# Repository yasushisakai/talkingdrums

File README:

sending and receiving protocol

[command, value, B00001010]

command
0: 'ready': first module to sender to say module is ready for getting byte
1: 'send' : message sent from sender to first module
2: 'receive' : message sent from the last module to the receiver

example:

[B00000000, B00000000, B00001010]
then
[B00000001, B10101010, B00001010]
.
.
.
[B00000010, B10101010, B00001010]

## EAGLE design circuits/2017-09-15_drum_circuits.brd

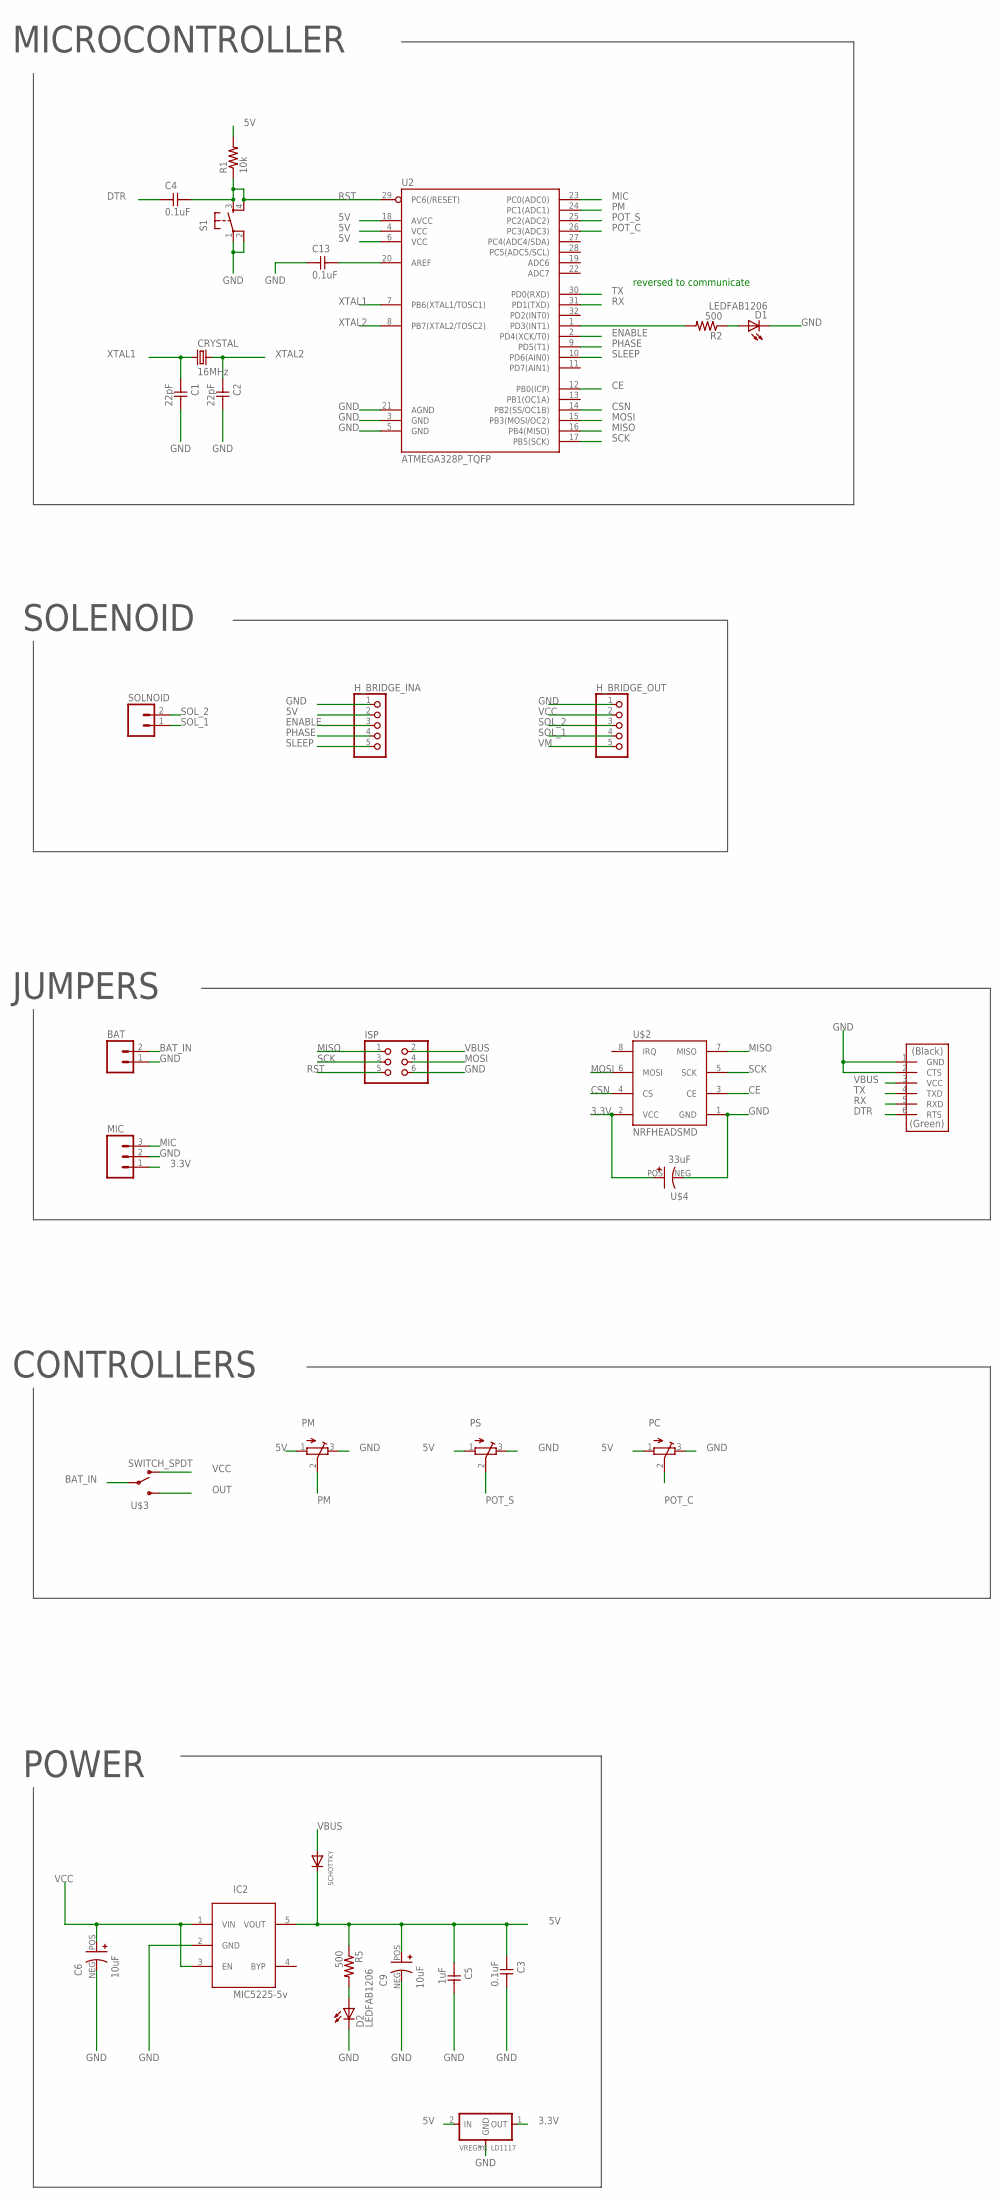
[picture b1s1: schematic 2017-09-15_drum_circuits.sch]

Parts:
BAT: M02PTH; 1X02
C1, C2: 22pF; C1206FAB
C3, C4, C13: 0.1uF; C1206FAB
C5: 1uF; C1206FAB
C6, C9: 10uF; PANASONIC-CAP-SMD-B
CRYSTAL: 16MHz; 2-SMD-5X3MM
D1, D2: LEDFAB1206; LED1206FAB
H_BRIDGE_INA: PINHD-1X05_2.54-SMD; 1X05SMD
H_BRIDGE_OUT: PINHD-1X05_2.54-SMD; 1X05SMD
IC2: MIC5225-5v; SOT23-5L
ISP: PINHD-2X3-SMD; 2X03SMD
MIC: M03PTH; 1X03
PC: TRIMPOTTC33X; TC33X
PM: TRIMPOTTC33X; TC33X
PS: TRIMPOTTC33X; TC33X
R1: 10k; R1206FAB
R2, R5: 500; R1206FAB
S1: 6MM_SWITCH6MM_SWITCH; 6MM_SWITCH
SCHOTTKY: DIODE_SOD-123FL; SOD-123FL
SOLNOID: M02PTH; 1X02
U2: ATMEGA328P_TQFP; TQFP32-08
U$1: FTDI-SMD-HEADER; 1X06SMD
U$2: NRFHEADSMD; 2.54MM
U$3: SWITCH_SPDT; KPS-1290
U$4: 33uF; PANASONIC-CAP-SMD-C
VREG3.3: LD1117; SOT23

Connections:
3.3V: MIC.1, U$2.2 (VCC), U$4.POS (+), VREG3.3.1 (OUT)
5V: C3.1, C5.1, C9.POS (+), H_BRIDGE_INA.2, IC2.5 (VOUT), PC.1 (A), PM.1 (A), PS.1 (A), R1.2, R5.1, SCHOTTKY.C, U2.4 (VCC), U2.6 (VCC), U2.18 (AVCC), VREG3.3.2 (IN)
BAT_IN: BAT.2, U$3.P
CE: U2.12 (PB0(ICP)), U$2.3 (CE)
CSN: U2.14 (PB2(SS/OC1B)), U$2.4 (CS)
DTR: C4.1, U$1.6 (RTS)
ENABLE: H_BRIDGE_INA.3, U2.2 (PD4(XCK/T0))
GND: BAT.1, C1.2, C2.2, C3.2, C5.2, C6.NEG (-), C9.NEG (-), C13.1, D1.2 (C), D2.2 (C), H_BRIDGE_INA.1, H_BRIDGE_OUT.1, IC2.2 (GND), ISP.6, MIC.2, PC.3 (E), PM.3 (E), PS.3 (E), S1.1, S1.2 (P1), U2.3 (GND), U2.5 (GND), U2.21 (AGND), U$1.1 (GND), U$1.2 (CTS), U$2.1 (GND), U$4.NEG (-), VREG3.3.3 (GND)
MIC: MIC.3, U2.23 (PC0(ADC0))
MISO: ISP.1, U2.16 (PB4(MISO)), U$2.7 (MISO)
MOSI: ISP.4, U2.15 (PB3(MOSI/OC2)), U$2.6 (MOSI)
unnamed: D1.1 (A), R2.1
unnamed: D2.1 (A), R5.2
unnamed: C13.2, U2.20 (AREF)
unnamed: R2.2, U2.1 (PD3(INT1))
OUT: U$3.S
PHASE: H_BRIDGE_INA.4, U2.9 (PD5(T1))
PM: PM.2 (S), U2.24 (PC1(ADC1))
POT_C: PC.2 (S), U2.26 (PC3(ADC3))
POT_S: PS.2 (S), U2.25 (PC2(ADC2))
RST: C4.2, ISP.5, R1.1, S1.3 (S), S1.4 (S1), U2.29 (PC6(/RESET))
RX: U2.31 (PD1(TXD)), U$1.5 (RXD)
SCK: ISP.3, U2.17 (PB5(SCK)), U$2.5 (SCK)
SLEEP: H_BRIDGE_INA.5, U2.10 (PD6(AIN0))
SOL_1: H_BRIDGE_OUT.4, SOLNOID.1
SOL_2: H_BRIDGE_OUT.3, SOLNOID.2
TX: U2.30 (PD0(RXD)), U$1.4 (TXD)
VBUS: ISP.2, SCHOTTKY.A, U$1.3 (VCC)
VCC: C6.POS (+), H_BRIDGE_OUT.2, IC2.1 (VIN), IC2.3 (EN), U$3.O
VM: H_BRIDGE_OUT.5
XTAL1: C1.1, CRYSTAL.P$1 (1), U2.7 (PB6(XTAL1/TOSC1))
XTAL2: C2.1, CRYSTAL.P$2 (2), U2.8 (PB7(XTAL2/TOSC2))

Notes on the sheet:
reversed to communicate
JUMPERS
MICROCONTROLLER
POWER
SOLENOID
CONTROLLERS

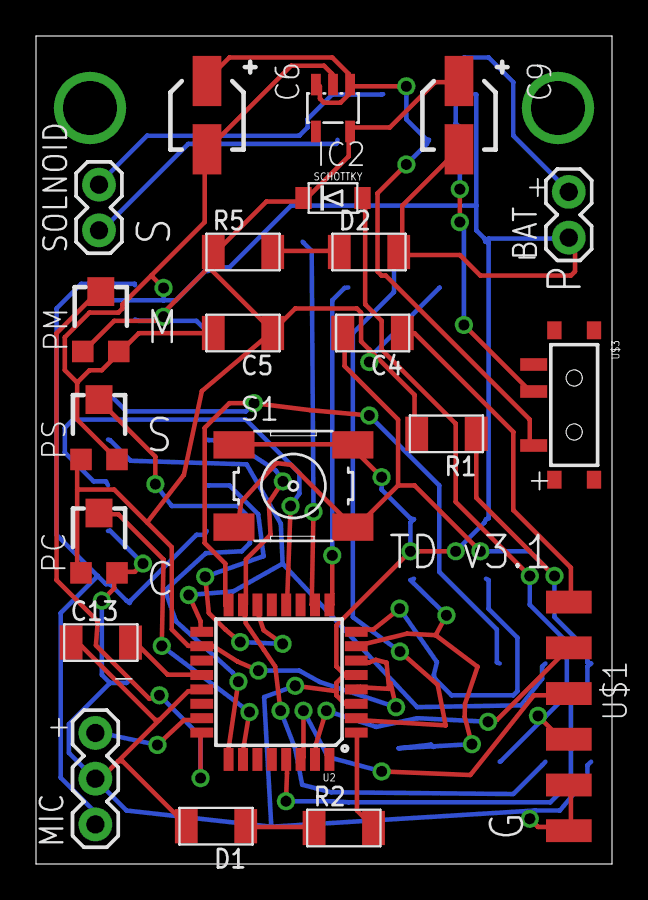
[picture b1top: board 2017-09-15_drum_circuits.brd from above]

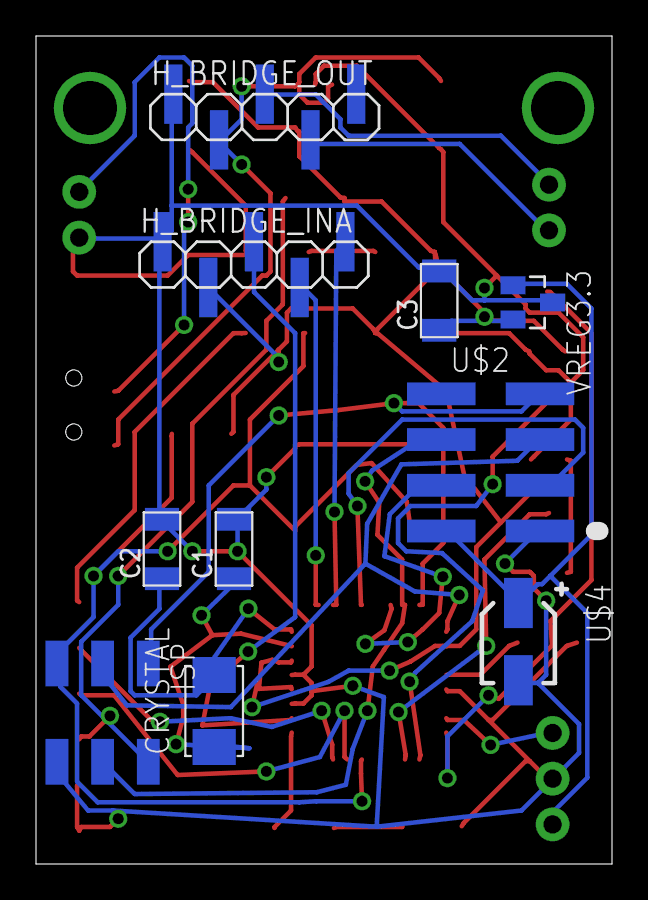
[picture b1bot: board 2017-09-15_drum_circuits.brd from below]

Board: 2 copper layers, 32.0 x 46.0 mm, 32 parts (10 on the bottom side), 30 nets.

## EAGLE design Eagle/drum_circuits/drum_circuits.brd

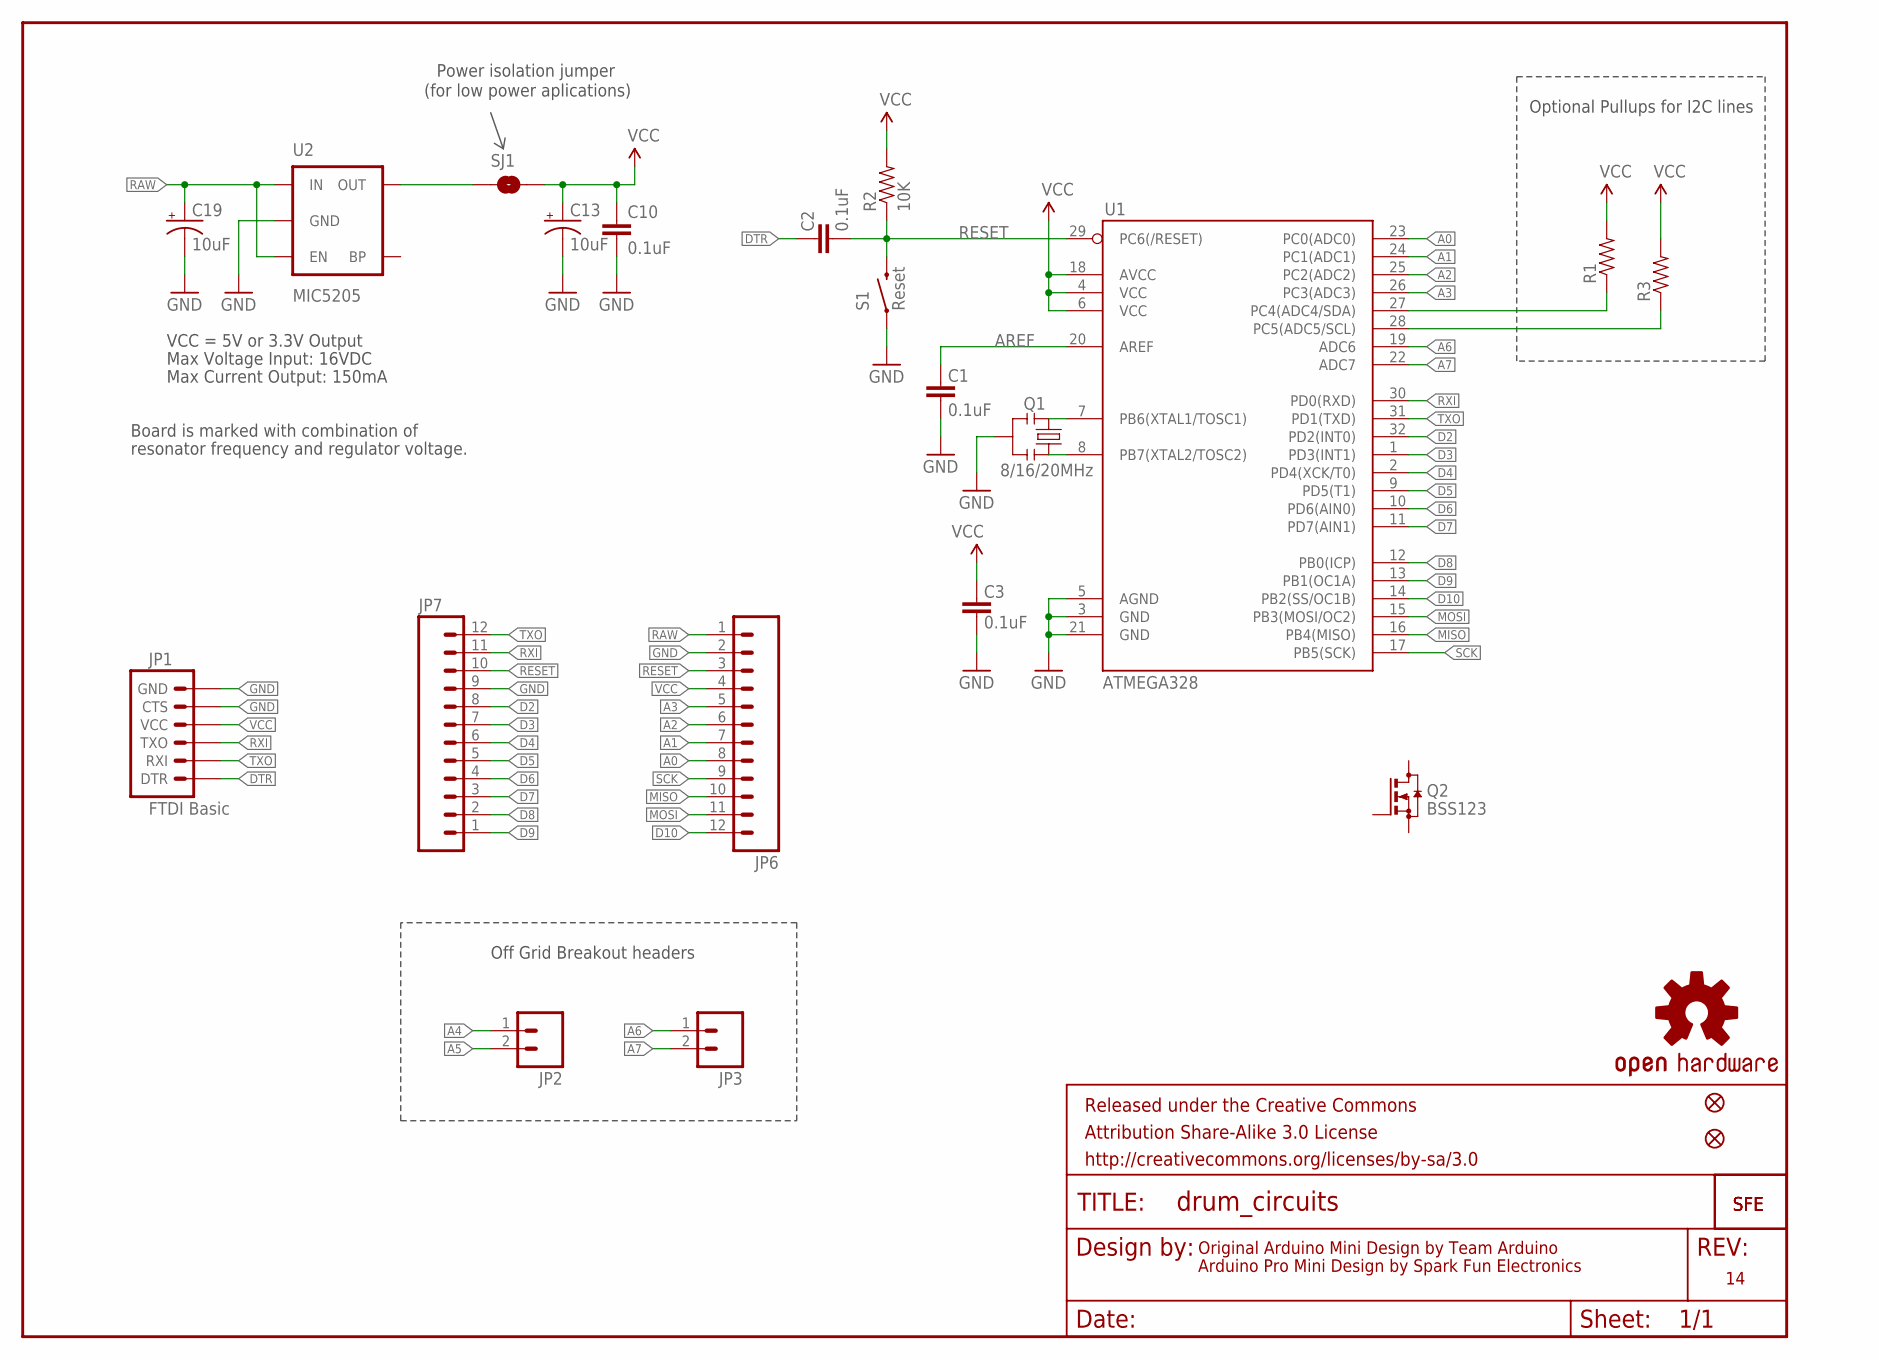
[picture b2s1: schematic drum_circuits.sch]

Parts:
C1, C2, C3, C10: 0.1uF; 0603-CAP
C13, C19: 10uF; EIA3216
FRAME1: FRAME-LETTER; CREATIVE_COMMONS
JP1: FTDI Basic; 1X06
JP2, JP3: M02PTH; 1X02
JP5, JP8: FIDUCIALUFIDUCIAL; MICRO-FIDUCIAL
JP6, JP7: M12PTH; 1X12
Q1: 8/16/20MHz; RESONATOR-SMD-1:1
Q2: BSS123; SOT23
R1, R3: RESISTOR0603-RES; 0603-RES
R2: 10K; 0603-RES
S1: Reset; TACTILE-SWITCH-SMD-ALT01
SJ1: SOLDERJUMPERNC; SJ_2S
U1: ATMEGA328; TQFP32-08
U2: MIC5205; SOT23-5
U$1: LOGO-SFESK; SFE-LOGO-FLAME
U$3: OSHW-LOGOS; OSHW-LOGO-S
U$11: LOGO-SFENEW; SFE-NEW-WEBLOGO

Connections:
A0: JP6.8, U1.23 (PC0(ADC0))
A1: JP6.7, U1.24 (PC1(ADC1))
A2: JP6.6, U1.25 (PC2(ADC2))
A3: JP6.5, U1.26 (PC3(ADC3))
A4: JP2.1, R1.1, U1.27 (PC4(ADC4/SDA))
A5: JP2.2, R3.1, U1.28 (PC5(ADC5/SCL))
A6: JP3.1, U1.19 (ADC6)
A7: JP3.2, U1.22 (ADC7)
AREF: C1.2, U1.20 (AREF)
D2: JP7.8, U1.32 (PD2(INT0))
D3: JP7.7, U1.1 (PD3(INT1))
D4: JP7.6, U1.2 (PD4(XCK/T0))
D5: JP7.5, U1.9 (PD5(T1))
D6: JP7.4, U1.10 (PD6(AIN0))
D7: JP7.3, U1.11 (PD7(AIN1))
D8: JP7.2, U1.12 (PB0(ICP))
D9: JP7.1, U1.13 (PB1(OC1A))
D10: JP6.12, U1.14 (PB2(SS/OC1B))
DTR: C2.2, JP1.1 (DTR)
GND: C1.1, C3.1, C10.2, C13.C (-), C19.C (-), JP1.5 (CTS), JP1.6 (GND), JP6.2, JP7.9, Q1.2, S1.1, S1.2 (1), U1.3 (GND), U1.5 (AGND), U1.21 (GND), U2.2 (GND)
MISO: JP6.10, U1.16 (PB4(MISO))
MOSI: JP6.11, U1.15 (PB3(MOSI/OC2))
unnamed: Q1.3, U1.8 (PB7(XTAL2/TOSC2))
unnamed: Q1.1, U1.7 (PB6(XTAL1/TOSC1))
unnamed: SJ1.1, U2.5 (OUT)
RAW: C19.A (+), JP6.1, U2.1 (IN), U2.3 (EN)
RESET: C2.1, JP6.3, JP7.10, R2.1, S1.3 (2), S1.4 (2), U1.29 (PC6(/RESET))
RXI: JP1.3 (TXO), JP7.11, U1.30 (PD0(RXD))
SCK: JP6.9, U1.17 (PB5(SCK))
TXO: JP1.2 (RXI), JP7.12, U1.31 (PD1(TXD))
VCC: C3.2, C10.1, C13.A (+), JP1.4 (VCC), JP6.4, R1.2, R2.2, R3.2, SJ1.2, U1.4 (VCC), U1.6 (VCC), U1.18 (AVCC)

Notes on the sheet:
Original Arduino Mini Design by Team Arduino
Arduino Pro Mini Design by Spark Fun Electronics
Max Voltage Input: 16VDC
Max Current Output: 150mA
Board is marked with combination of
resonator frequency and regulator voltage.
VCC = 5V or 3.3V Output
Optional Pullups for I2C lines
Off Grid Breakout headers
Power isolation jumper
(for low power aplications)

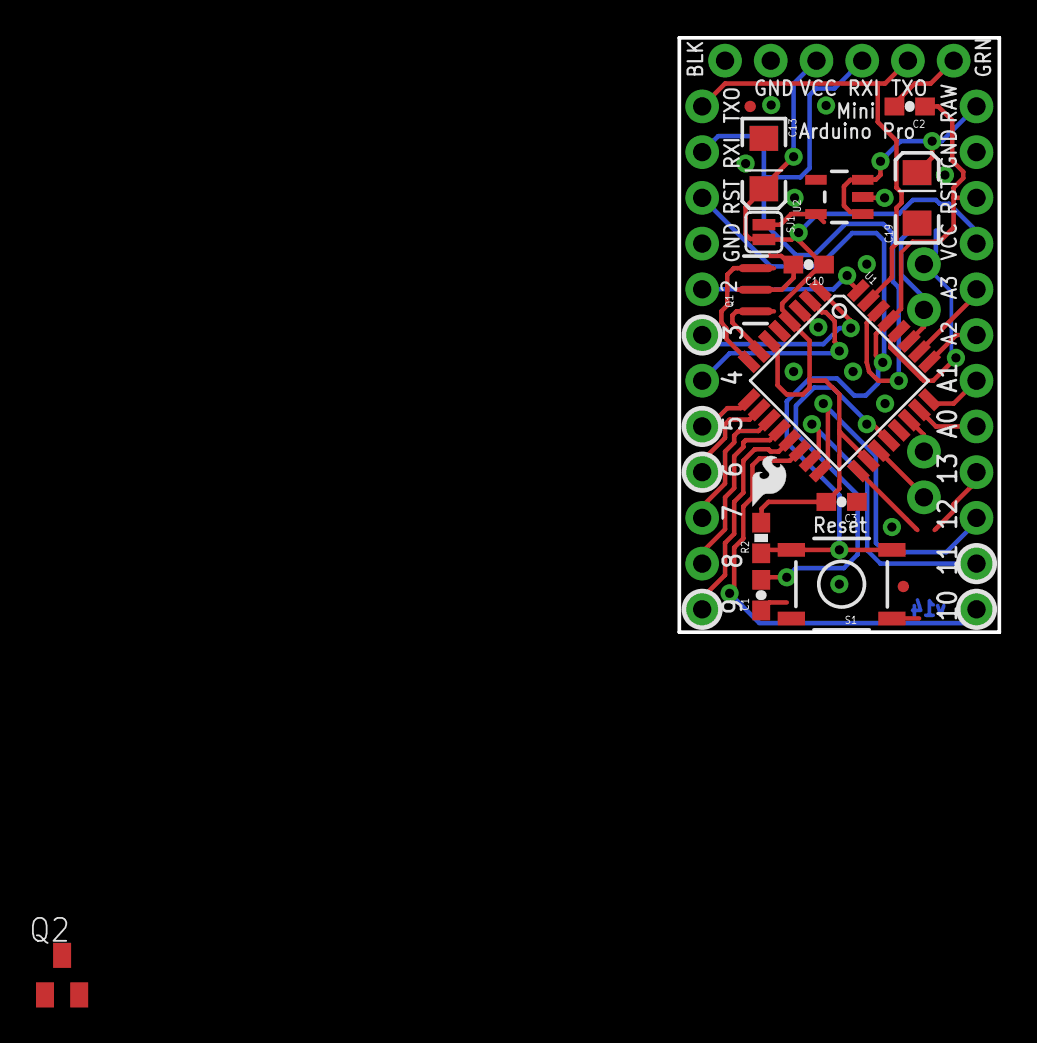
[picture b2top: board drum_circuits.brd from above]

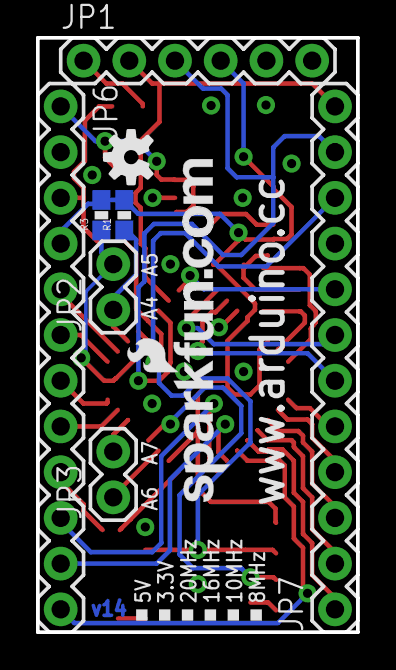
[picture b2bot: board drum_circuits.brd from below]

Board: 2 copper layers, 17.8 x 33.0 mm, 26 parts (9 on the bottom side), 31 nets.

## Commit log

2016-06-28 arduino microphone
2016-06-28 added sparkfun arduino reference board
2016-06-28 did it merge?
2016-06-28 gitignore mac
2016-06-28 test sequence
2016-06-29 sequence microphone
2016-06-29 hit solenoid
2016-06-29 init sequence
2016-06-30 fix bugs with timer
2016-06-30 missing amperson
2016-07-06 updated code
2016-07-06 RF examples
2016-07-08 master slave arduino projects
2016-07-26 trasmision working
2016-07-26 avg code and replay three times
2016-07-26 play sequence
2016-07-26 working version send
2016-07-26 finally started the schematic
2016-07-31 deleted Adaruit Pro trinket
2016-07-31 understanding being a slave
2016-08-01 schematics
2016-08-01 added Utilities
2016-08-04 slave rewrite
2016-08-04 code cleanup
2016-08-04 gitignore
2016-08-04 new version of slave
2016-08-05 housekeeping
2016-08-05 changed solpin to 3->5to PMW
2016-08-08 recommit
2016-08-11 Serial in (reader)
2016-08-14 image sender cinder app
2016-08-15 pixeleted image
2016-08-15 pixels
2016-08-15 updated master
2016-08-16 updated slave and cinder_in
2016-08-16 iteration pixel
2016-08-16 working iteration through colors
2016-08-16 Serial comunication CinderIn
2016-08-16 refactor clock, server, server_slave
2016-08-16 server_slave
2016-08-16 fixed reset values
2016-08-16 updated debug flags in slave
2016-08-16 deleted unneeded source
2016-08-16 ffdds
2016-08-16 images
2016-08-16 xcode ignore
2016-08-17 xcode env
2016-08-17 udpate cinder
2016-08-17 git clean
2016-08-17 deleted reciever
2016-08-17 Squashed commit of the following:
    commit abe85c2966fc92396aad66928a0efb65dd57af0f
    Merge: c9d806f 01d28d6
    Author: Yasushi Sakai <ysshski@gmail.com>
    Date: Wed Aug 17 15:28:15 2016 -0400
    ??
    commit c9d806f6b5e07283ada4fb7191bae6b421da50e0
2016-08-17 fix timing in server/clients
2016-08-18 fix incoming msg
2016-08-18 test ImageReciever @Utilites/Serial Communication
2016-08-19 ImageReciever update. working but having CGContextFlush
2016-08-23 reciever surface version
2016-08-24 slave_server
2016-08-24 fixed byte error in format
2016-08-25 clock changes
2016-08-25 sensing byte sever
2016-08-31 slave updated to read 0B00000001
2016-08-31 got rid of ‘0’ before B
2016-08-31 scrambling image
2016-08-31 restructuring branches
2016-08-31 created readme.md to direct to project page
2016-08-31 Serial Communication Test 2
2016-09-01 before dev
2016-09-01 update slave
2016-09-01 updatede slave states
2016-09-01 sending
2016-09-01 review on slave code
2016-09-01 fix to solve confilct
2016-09-01 fixed times
2016-09-01 timing fix
2016-09-01 clocks change
2016-09-02 clock counter
2016-09-02 updated time sync with slave and server
2016-09-03 clock
2016-09-03 clean up
2016-09-03 changed baud for reciever
2016-09-03 update play sequence
2016-09-03 fix times
2016-09-03 slave reads 11bits
2016-09-03 updated sequence with headers
2016-09-04 Image Sender saving image
2016-09-05 new slave
2016-09-05 ordering and clean up
2016-09-05 Image Reciver knows head detection
2016-09-06 clean receiver cinder
2016-09-06 pixel count
2016-09-07 reciver
2016-09-07 updated render
2016-09-08 debug
2016-09-08 slave
2016-09-08 silly mistakes
2016-09-08 fix bugs
2016-09-08 avg slave
2016-09-08 little change
2016-09-08 mic test
2016-09-09 upadated
2016-09-11 fix timing" " ;
2016-09-11 seperated hit and tick
2016-09-14 msg fix timing and prints
2016-09-14 fix sequence and debug prints
2016-09-14 fix play times
2016-09-15 new sequence process, auto-calibration threshold, new test and calibration process
2016-09-15 clean signal sensitivity
2016-09-15 debug off
2016-09-15 play 3 times header
2016-09-15 slave header check
2016-09-16 9 digit header reading correction with ave.
2016-09-17 fix headers
2016-11-28 fft, test codes
2016-11-28 add fft
2016-11-28 fft lib
2016-11-29 organized, signal processing approaches
2016-11-30 new test files, mics, fth, fft
2016-12-01 filters
2016-12-02 test case filters
2016-12-05 fix timing bugs, band pass filter
2016-12-05 refactor test
2016-12-05 added circuit files
2016-12-05 fix dynamic memory calls
2016-12-05 clean code
2016-12-05 schematics and parts_list
2016-12-05 calibrated hits
2016-12-06 clean code, merge server slave
2016-12-06 fixed slave times
2016-12-06 fixed server automatic start to send
2016-12-06 fix server no playing sequence
2016-12-06 slave fix header
2016-12-06 fixed header sequence
2016-12-06 header working for server and client
2016-12-06 categorize parts
2016-12-06 header
2016-12-07 fixed sender/receiver cinder
2016-12-07 fixed cinder received bit convertion
2016-12-07 fixed no playing header
2016-12-07 syncronized index on cinder
2016-12-07 fixed send images
2016-12-09 parts csv and schematic without mic
2016-12-13 sxsw
2016-12-14 dadad
2016-12-14 test mic
2016-12-14 music
2016-12-15 clock times
2016-12-16 updated dynamic clock:
2016-12-16 clock server
2016-12-16 processing reciever
2016-12-17 memsg
2016-12-17 cneter
2016-12-17 sender gray
2016-12-21 final changes class
2016-12-21 image layout:
2016-12-21 format
2016-12-21 nested'
2016-12-21 image
2016-12-21 class img
2016-12-21 img t
2016-12-21 row img
2016-12-21 gh-pages
2016-12-21 house keeping
2016-12-21 hide address bar in mobile devices
2016-12-21 hide URL2
2016-12-22 adding nicole's instagram comment
2016-12-27 video tag
2017-03-24 clean tomas
2017-04-25 fixed dropbox broken link
2017-09-13 arduino
2017-09-14 overwriting board & schematic from 5d2ad6c18a5f5ec5e8afae34b5d28b62efabe567
2017-09-15 new drum circuits
2017-09-15 cleaned circuits folder
2017-09-19 modified Working Version Media Lab clock
2017-09-19 before message protocol
2017-09-19 processing serial
2017-09-19 modules created and clock modes
2017-09-20 new clock sending 2 bytes
2017-09-20 server clk, mic, solenoid
2017-09-20 in the middle of changinge Processing SendClockCommands
2017-09-20 clock sending three bytes
2017-09-20 clock modes
2017-09-20 debug mode
2017-09-21 input
2017-09-26 received and sender
2017-09-26 transfer complete
2017-09-26 interface b
2017-09-26 instructions
2017-10-09 flash
2018-02-23 script to send my own ip
2018-02-23 minor change in ip script
2018-02-23 get ip for linux
2018-03-04 updated readme for processing sketch autostart
2018-03-05 imageSender (OF)
2018-03-05 raspi doesn't like pngs...
2018-03-06 imageReciever, confirmed output from deivce gitignores
2018-03-07 at least receiver builds and runs
2018-03-07 small mod in sender
2018-03-07 deleted wierd gitignore
2018-03-07 does its job
2018-07-02 new eagle
2018-07-02 clean files
2018-07-03 windows version of sender and receiver
2018-07-23 cleeeeean up
2018-07-23 latest start and end
2018-07-23 updated server
2018-07-23 added batch files
2018-07-23 server update, get pixel test
2018-07-28 server and sender update
2018-07-28 client side sketch for remoteltly start and stop sending from server
2018-07-28 try catch again
2018-07-28 try for receiver
2018-07-28 receiver fullScreen
2018-07-28 server update; image and endpoints now connect
2018-07-30 major update on server
2018-07-30 sender and receiver updated for the new endpoints
2018-07-30 sender Serial.write() change
2018-07-31 ui improvements for receiver and sender
2018-07-31 enum mistake
2018-07-31 minor sender typos
2018-07-31 receiver typos
2018-07-31 arduino test serial_write modified to test sending bytes, not the protocol
2018-07-31 server change?
2018-08-01 arduino test write, sending three values
2018-08-03 ftdi cable script
2018-08-05 updated slave, communication
2018-08-05 updated clock
2018-08-05 clean variables
2018-08-05 more clean up
2018-08-05 more clean
2018-08-05 clean
2018-08-05 clean circuits and modules
2018-08-05 updated protocol
2018-08-06 serial sender
2018-08-06 baud rate back to 115200
2018-08-06 serial communication protocol
2018-08-06 updated comunication
2018-08-06 sender and receiver update for new protocol
2018-08-06 minor debug logging
2018-08-07 exceptions on invalid short messages
2018-08-11 img visualizer
2018-08-11 sender and receiver img display
2018-08-11 sender receiver img update
2018-08-11 update sender
2018-08-11 rotate sender
2018-08-12 safe check
2018-08-12 loader pde
2018-08-12 image url
2018-08-12 cursors
2018-08-12 try catch on load image
2018-08-12 receiver error img check
2018-08-12 times receiver
2018-08-13 removed old server submodule (yasushisakai/simpleWebApp)
2018-08-17 server submodule pointing to rust

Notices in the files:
parts and their libraries:
SparkFun-DigitalIC: Licensing: Creative Commons ShareAlike 4.0 International - https://creativecommons.org/licenses/by-sa/4.0
SparkFun-Aesthetics: Licensing: CC v3.0 Share-Alike You are welcome to use this library for commercial purposes.
SparkFun-Aesthetics: Released under the Creative Commons
